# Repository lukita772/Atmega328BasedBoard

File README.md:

# Atmega328BasedBoard

[Schematic.pdf](https://github.com/lukita772/Atmega328BasedBoard/files/13856203/Schematic.pdf)

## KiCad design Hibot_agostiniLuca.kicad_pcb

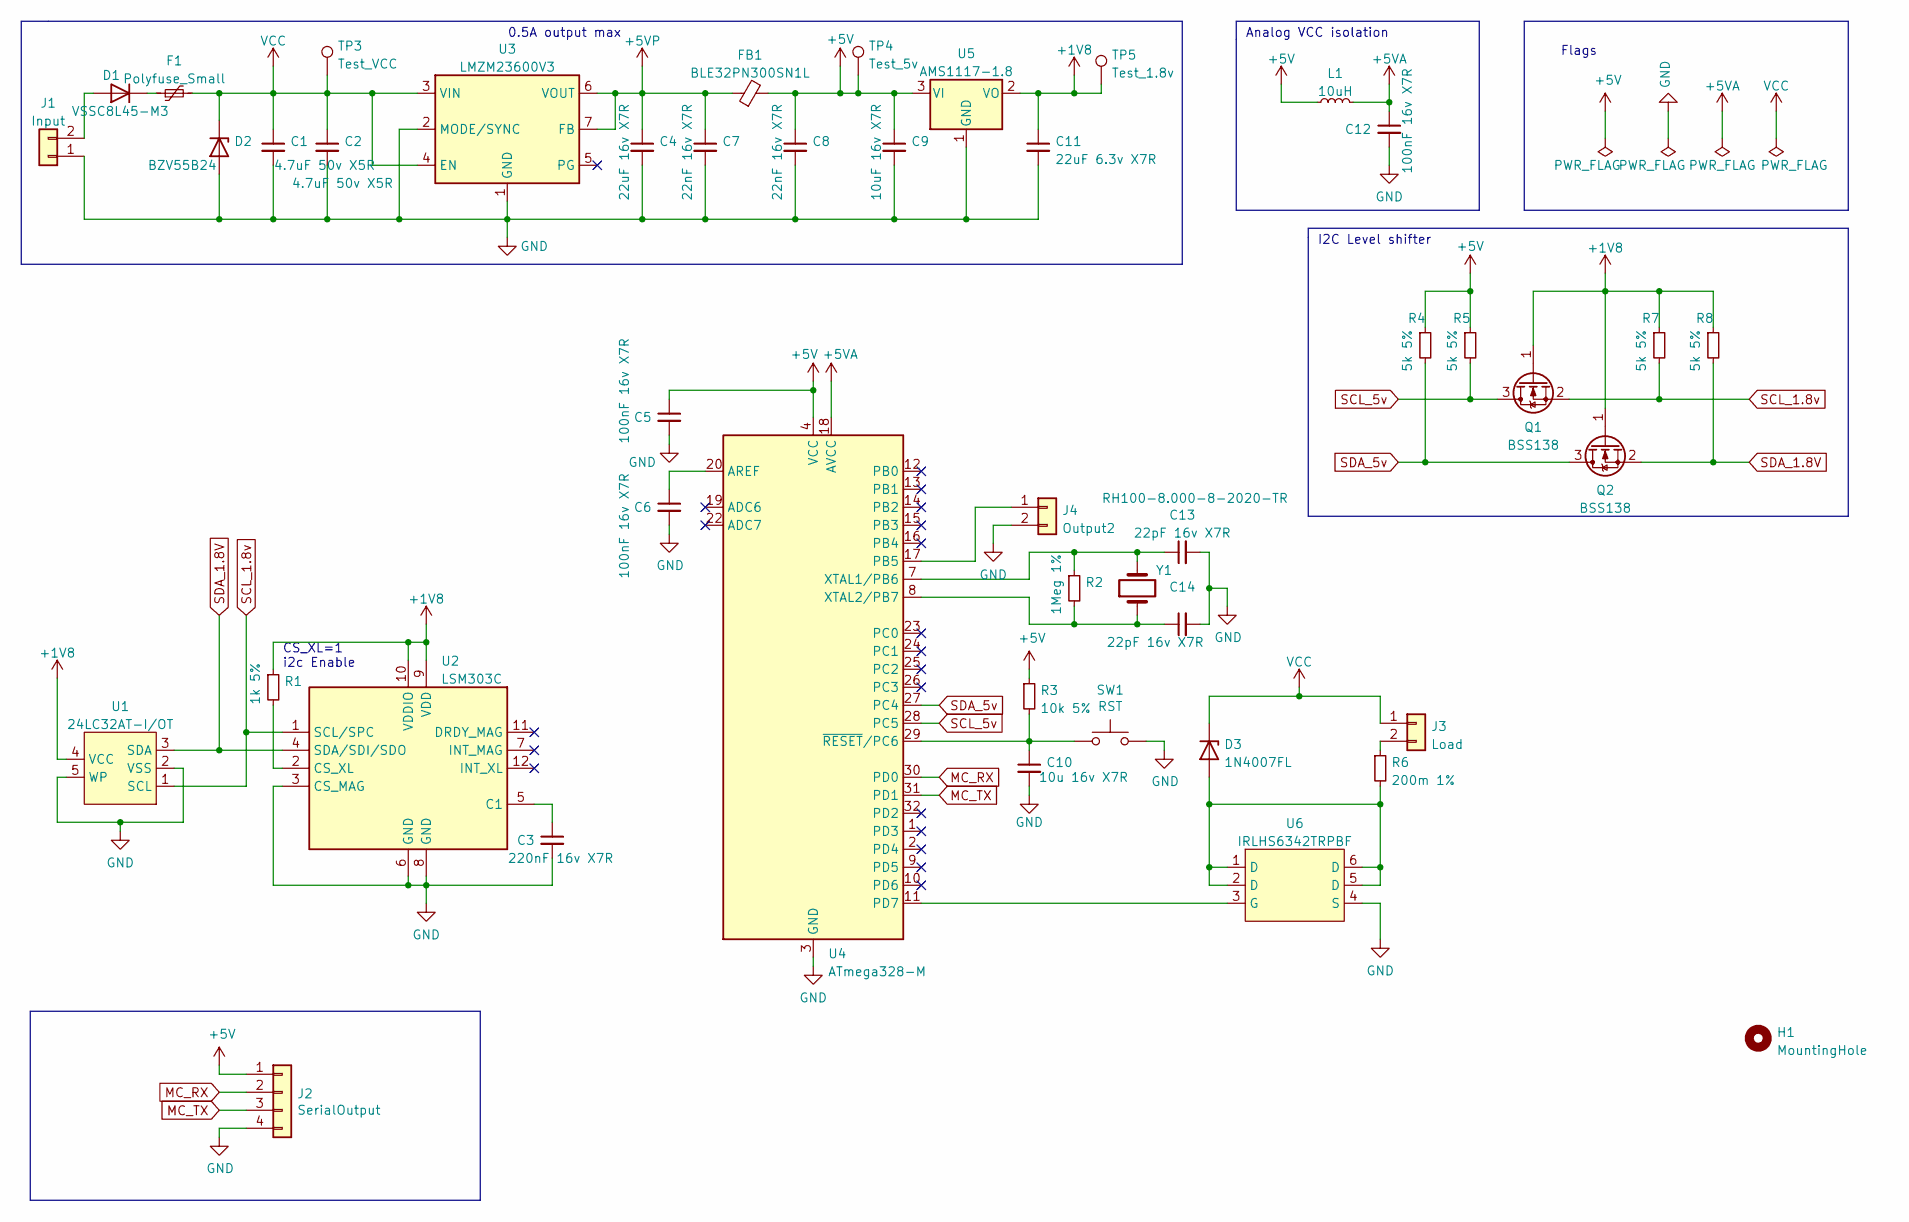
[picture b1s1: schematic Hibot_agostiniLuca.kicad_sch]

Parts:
C1, C2: 4.7uF 50v X5R; C_1206_3216Metric
C3: 220nF 16v X7R; C_0805_2012Metric
C4: 22uF 16v X7R; C_0603_1608Metric
C5, C6: 100nF 16v X7R; C_0603_1608Metric
C7, C8: 22nF 16v X7R; C_0603_1608Metric
C9: 10uF 16v X7R; C_0805_2012Metric
C10: 10u 16v X7R; C_0805_2012Metric
C11: 22uF 6.3v X7R; C_0805_2012Metric
C12: 100nF 16v X7R; C_0805_2012Metric
C13, C14: 22pF 16v X7R; C_0603_1608Metric
D1: VSSC8L45-M3; D_2512_6332Metric
D2: BZV55B24; D_MiniMELF
D3: 1N4007FL; D_0805_2012Metric
F1: Polyfuse_Small; C_Disc_D3.0mm_W1.6mm_P2.50mm
FB1: BLE32PN300SN1L; R_1210_3225Metric_Pad1.30x2.65mm_HandSolder
H1: MountingHole; MountingHole_2.2mm_M2_DIN965_Pad
J1: Input; TerminalBlock_Phoenix_MPT-0,5-2-2.54_1x02_P2.54mm_Horizontal
J2: SerialOutput; TerminalBlock_Phoenix_MPT-0,5-4-2.54_1x04_P2.54mm_Horizontal
J3: Load; TerminalBlock_Phoenix_MPT-0,5-2-2.54_1x02_P2.54mm_Horizontal
J4: Output2; TerminalBlock_Phoenix_MPT-0,5-2-2.54_1x02_P2.54mm_Horizontal
L1: 10uH; L_0201_0603Metric
Q1, Q2: BSS138; SOT-23
R1: 1k 5%; R_0603_1608Metric
R2: 1Meg 1%; R_0603_1608Metric
R3: 10k 5%; R_0603_1608Metric
R4, R5, R7, R8: 5k 5%; R_0603_1608Metric
R6: 200m 1%; R_0603_1608Metric
SW1: RST; SW_SPST_B3U-1000P
TP3: Test_VCC; TestPoint_Pad_D1.0mm
TP4: Test_5v; TestPoint_Pad_D1.0mm
TP5: Test_1.8v; TestPoint_Pad_D1.0mm
U1: 24LC32AT-I/OT; SOT-23-5
U2: LSM303C; LGA-12_2x2mm_P0.5mm
U3: LMZM23600V3; Texas_SIL0010A_MicroSiP-10-1EP_3.8x3mm_P0.6mm_EP0.7x2.9mm_T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
U4: ATmega328-M; QFN-32-1EP_5x5mm_P0.5mm_EP3.1x3.1mm
U5: AMS1117-1.8; SOT-223-3_TabPin2
U6: IRLHS6342TRPBF; TRANS_IRL100HS121
Y1: RH100-8.000-8-2020-TR; Crystal_SMD_Abracon_ABM10-4Pin_2.5x2.0mm

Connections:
+1V8: C11.1, Q1.1 (G), Q2.1 (G), R1.1, R7.1, R8.1, TP5.1, U1.4 (VCC), U2.9 (VDD), U2.10 (VDDIO), U5.2 (VO)
+5V: C5.1, C8.1, C9.1, FB1.2, J2.1, L1.1, R3.1, R4.1, R5.1, TP4.1, U4.4 (VCC), U4.6 (VCC), U5.3 (VI)
+5VA: C12.1, L1.2, U4.18 (AVCC)
+5VP: C4.1, C7.1, FB1.1, U3.6 (VOUT), U3.7 (FB)
GND: C1.2, C2.2, C3.2, C4.2, C5.2, C6.2, C7.2, C8.2, C9.2, C10.2, C11.2, C12.2, C13.2, C14.2, D2.2 (A), J1.1, J2.4, J4.2, SW1.2, U1.2 (VSS), U1.5 (WP), U2.3 (CS_MAG), U2.6 (GND), U2.8 (GND), U3.1 (GND), U3.2 (MODE/SYNC), U3.11 (GND), U4.3 (GND), U4.5 (GND), U4.21 (GND), U4.33 (GND), U5.1 (GND), U6.4 (S)
MC_RX: J2.2, U4.30 (PD0)
MC_TX: J2.3, U4.31 (PD1)
unnamed: C3.1, U2.5 (C1)
unnamed: C6.1, U4.20 (AREF)
unnamed: C10.1, R3.2, SW1.1, U4.29 (~RESET/PC6)
unnamed: C13.1, R2.1, U4.7 (XTAL1/PB6), Y1.2
unnamed: C14.1, R2.2, U4.8 (XTAL2/PB7), Y1.1
unnamed: D1.1 (K), F1.1
unnamed: D1.2 (A), J1.2
unnamed: D3.2 (A), R6.2, U6.1 (D), U6.2 (D), U6.5 (D), U6.6 (D)
unnamed: J3.2, R6.1
unnamed: J4.1, U4.17 (PB5)
unnamed: R1.2, U2.2 (CS_XL)
unnamed: U4.11 (PD7), U6.3 (G)
SCL_1.8v: Q1.2 (S), R7.2, U1.1 (SCL), U2.1 (SCL/SPC)
SCL_5v: Q1.3 (D), R5.2, U4.28 (PC5)
SDA_1.8V: Q2.2 (S), R8.2, U1.3 (SDA), U2.4 (SDA/SDI/SDO)
SDA_5v: Q2.3 (D), R4.2, U4.27 (PC4)
VCC: C1.1, C2.1, D2.1 (K), D3.1 (K), F1.2, J3.1, TP3.1, U3.3 (VIN), U3.4 (EN)

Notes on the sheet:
Analog VCC isolation
CS_XL=1 i2c Enable
0.5A output max
I2C Level shifter
Flags

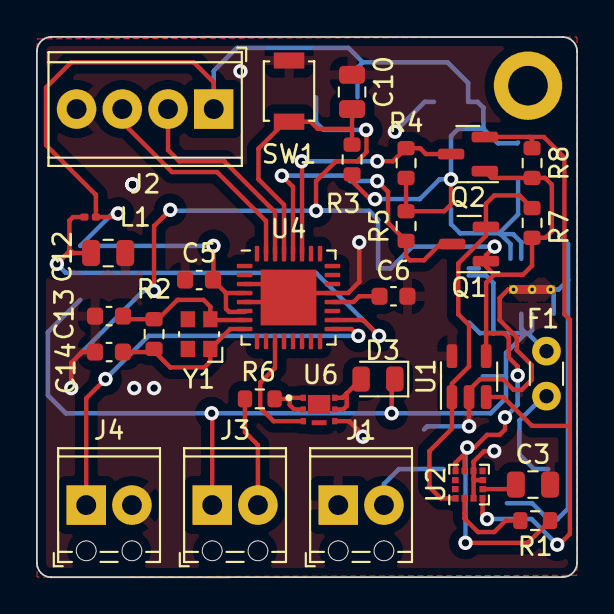
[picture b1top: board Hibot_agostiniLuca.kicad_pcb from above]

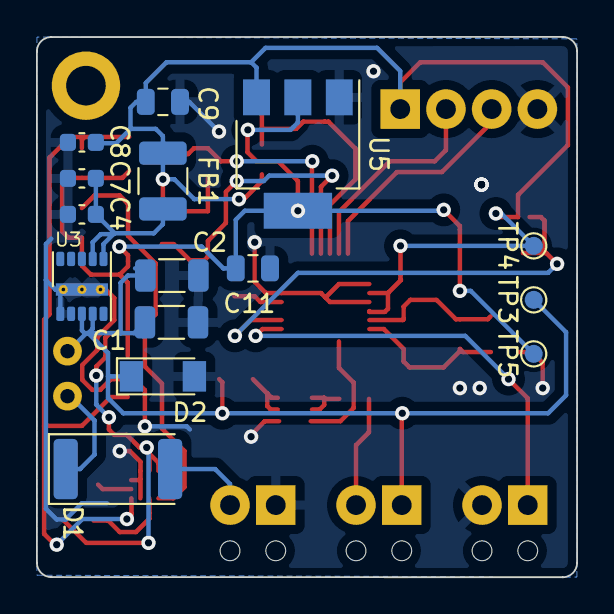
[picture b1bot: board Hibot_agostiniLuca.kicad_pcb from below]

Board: 2 copper layers, 30.0 x 30.0 mm, 46 parts (15 on the bottom side), 24 nets.
